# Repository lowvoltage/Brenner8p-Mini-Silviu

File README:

Minor variations on the PCB layout of the Brenner8p Mini (by Silviu) PIC programmer

Original design: 
http://www.sprut.de/electronic/pic/projekte/brenner8/
http://www.sprut.de/electronic/pic/projekte/brenner8mini/index.htm#p

Author: Dimitar Kovachev, http://lowvoltage.wordpress.com/

Released under the Creative Commons Attribution Share-Alike 3.0 license
http://creativecommons.org/licenses/by-sa/3.0/

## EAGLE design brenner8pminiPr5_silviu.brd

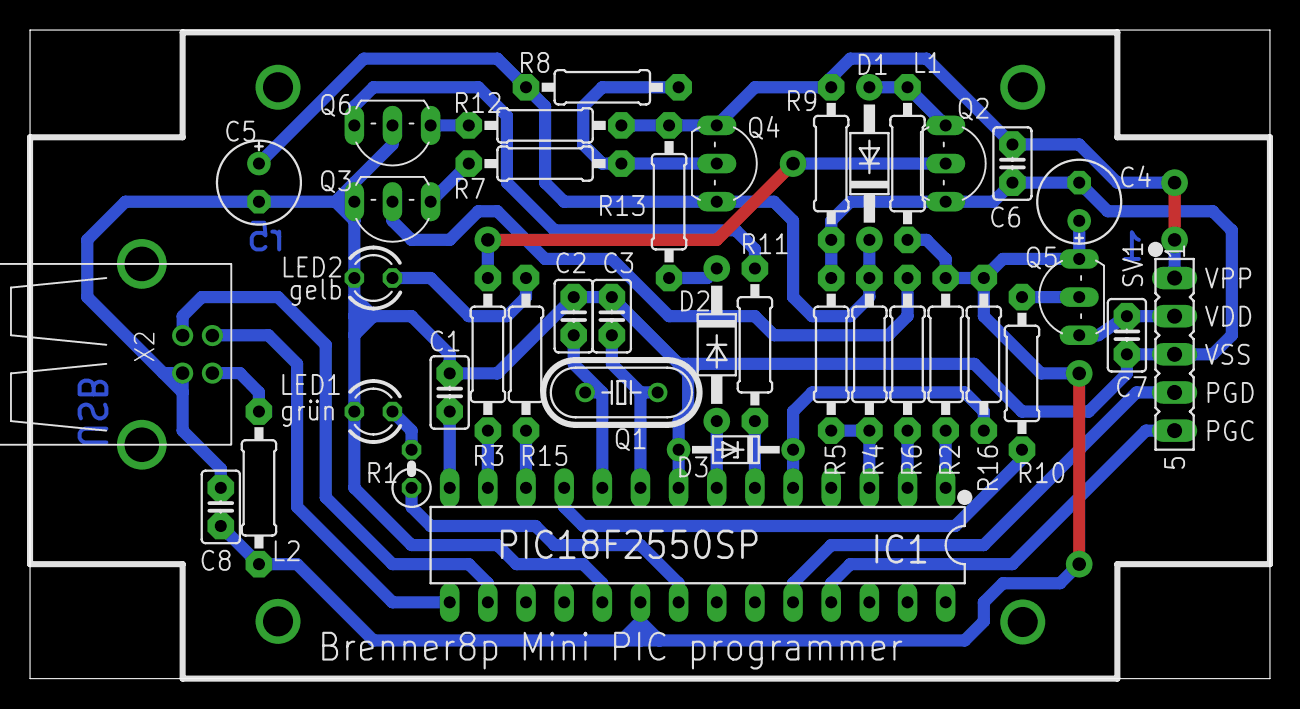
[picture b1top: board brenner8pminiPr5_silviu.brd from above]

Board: 2 copper layers, 82.5 x 43.2 mm, 39 parts (0 on the bottom side), 34 nets.

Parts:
C1: 220nF; C025-025X050
C2, C3: 22p; C025-025X050
C4: 10µF; E2,5-6E
C5: 47µF; E2,5-6E
C6: 1nF; C025-025X050
C7, C8: 100nF; C025-025X050
D1, D2: BAT43; DO41-10
D3: 3,3V; DO34Z7
IC1: PIC18F2550SP; DIL28-3
L1: 680µH; 0207/10
L2: 10µH; 0207/10
LED1: grün; LED3MM
LED2: gelb; LED3MM
Q1: 20 MHz; HC49/S
Q2, Q3: BC338-25; TO92-EBC
Q4, Q5: BC328-25; TO92-EBC
Q6: BF959; TO92-BEC
R1: 1k; 0207/2V
R2: 10 k; 0207/10
R3, R6, R7, R9, R10, R11: 10k; 0207/10
R4: 4k7; 0207/10
R5: 2k2; 0207/10
R8: 100k; 0207/10
R12, R13: 100; 0207/10
R15: 1 k; 0207/10
R16: 330; 0207/10
SV1: ICSP; FE05-1
X2: USB-B-H

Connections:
+12V: C5.+, D1.C, Q4.E, R4.2, R8.2
CLOCK_18: IC1.25, SV1.5
DATA_18: IC1.24, SV1.4
unnamed: IC1.15, X2.D-
unnamed: IC1.16, X2.D+
unnamed: L2.1, X2.VBUS
unnamed: LED1.A, R1.2
unnamed: C1.1, IC1.14
unnamed: C2.1, IC1.10, Q1.1
unnamed: C3.1, IC1.9, Q1.2
unnamed: IC1.1, R2.1
unnamed: Q5.B, R10.2
unnamed: IC1.12, R15.2
unnamed: IC1.11, R10.1
unnamed: LED2.A, R15.1
unnamed: D1.A, L1.2, Q2.C
unnamed: Q2.B, R3.1
unnamed: IC1.13, R3.2
unnamed: IC1.21, R1.1
unnamed: C7.1, Q5.C, SV1.2
unnamed: IC1.3, R4.1, R5.2
unnamed: Q6.B, R11.2
unnamed: IC1.6, R11.1
unnamed: Q3.B, R6.1
unnamed: Q6.C, R12.1
unnamed: Q3.C, R7.1
unnamed: Q4.B, R7.2, R8.1
unnamed: D2.A, IC1.7
unnamed: D2.C, R13.1
unnamed: IC1.2, R6.2
UREF: D3.C, IC1.5, R16.1
VDD: C4.+, C8.1, IC1.20, L1.1, L2.2, Q5.E, R2.2, R16.2
VPP_8_14_18: C6.1, Q4.C, R9.2, R12.2, R13.2, SV1.1
VSS: C1.2, C2.2, C3.2, C4.-, C5.-, C6.2, C7.2, C8.2, D3.A, IC1.8, IC1.19, LED1.K, LED2.K, Q2.E, Q3.E, Q6.E, R5.1, R9.1, SV1.3, X2.GND

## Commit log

2012-07-07 Initial version with the original files (Eagle v5)
2012-07-07 Resaved in v.6 format
2012-07-07 Fixed via sizes. Vias for mounting holes. DRC fixes
2012-07-07 Reorder components and fix DRC errors
2012-07-07 Smaller cap footprint
2012-07-07 Reduced pad sizes
2012-07-07 Snap components to grid 50. Labels fix
2012-07-07 Fixed D2-D3 overlap
2012-07-07 Removed layer 116
2012-07-07 Display some values
2012-07-08 Fixed DRC clearances and pad shapes
2012-07-08 Added silkscreen labels. Final DRC error fixes
2012-07-08 Rectangular dimensions
2012-07-08 Metric drills
2012-07-08 Header drill size set to 1mm
